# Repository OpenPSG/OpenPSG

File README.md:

# OpenPSG

## Notes

This tool will only work on Google Chrome, Microsoft Edge or Android. It will
not work on Firefox, Safari, or any other browser.

On Linux you'll need to explicitly enable the Web Bluetooth API in your
browser settings. This is still an experimental feature due to historical
issues with the Linux Bluetooth stack. If you are running an up-to-date
Linux install you'll be totally fine to turn it on!

https://github.com/WebBluetoothCG/web-bluetooth/blob/main/implementation-status.md

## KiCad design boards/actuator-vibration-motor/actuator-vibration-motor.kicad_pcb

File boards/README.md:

# Board Files

The boards are designed with/for KiCad v8.0.x

## JLCPCB Manufacturing and Assembly

### Gerbers and Drill Files

Follow the instructions here:

https://jlcpcb.com/help/article/how-to-generate-gerber-and-drill-files-in-kicad-8

### Bill of Materials (BOM)

In eeschema, go to `Tools` -> `Generate Bill of Materials`.

In the edit tab configure the fields as follows:

Then click on `Generate` and save the file as `<board>-bom.csv` in the manufacturing files folder.

### Pick and Place (CPL)

In pcbnew, go to `File` -> `Fabrication Outputs` -> `Component Placement (.pos, .gbr)...`.

Configure the fields as follows:

Then click on `Generate`.

### Convert to JLCPCB Format

Use my [jlcfabtool](https://github.com/dpeckett/jlcfabtool) utility to convert the files to the JLCPCB format.

```sh
jlcfabtool bom convert <board>-bom.csv
jlcfabtool placement convert <board>-all-pos.csv
```

### Create the Archive

```sh
cd <board>
zip -r ../$(basename "$(pwd)").zip ./*
```

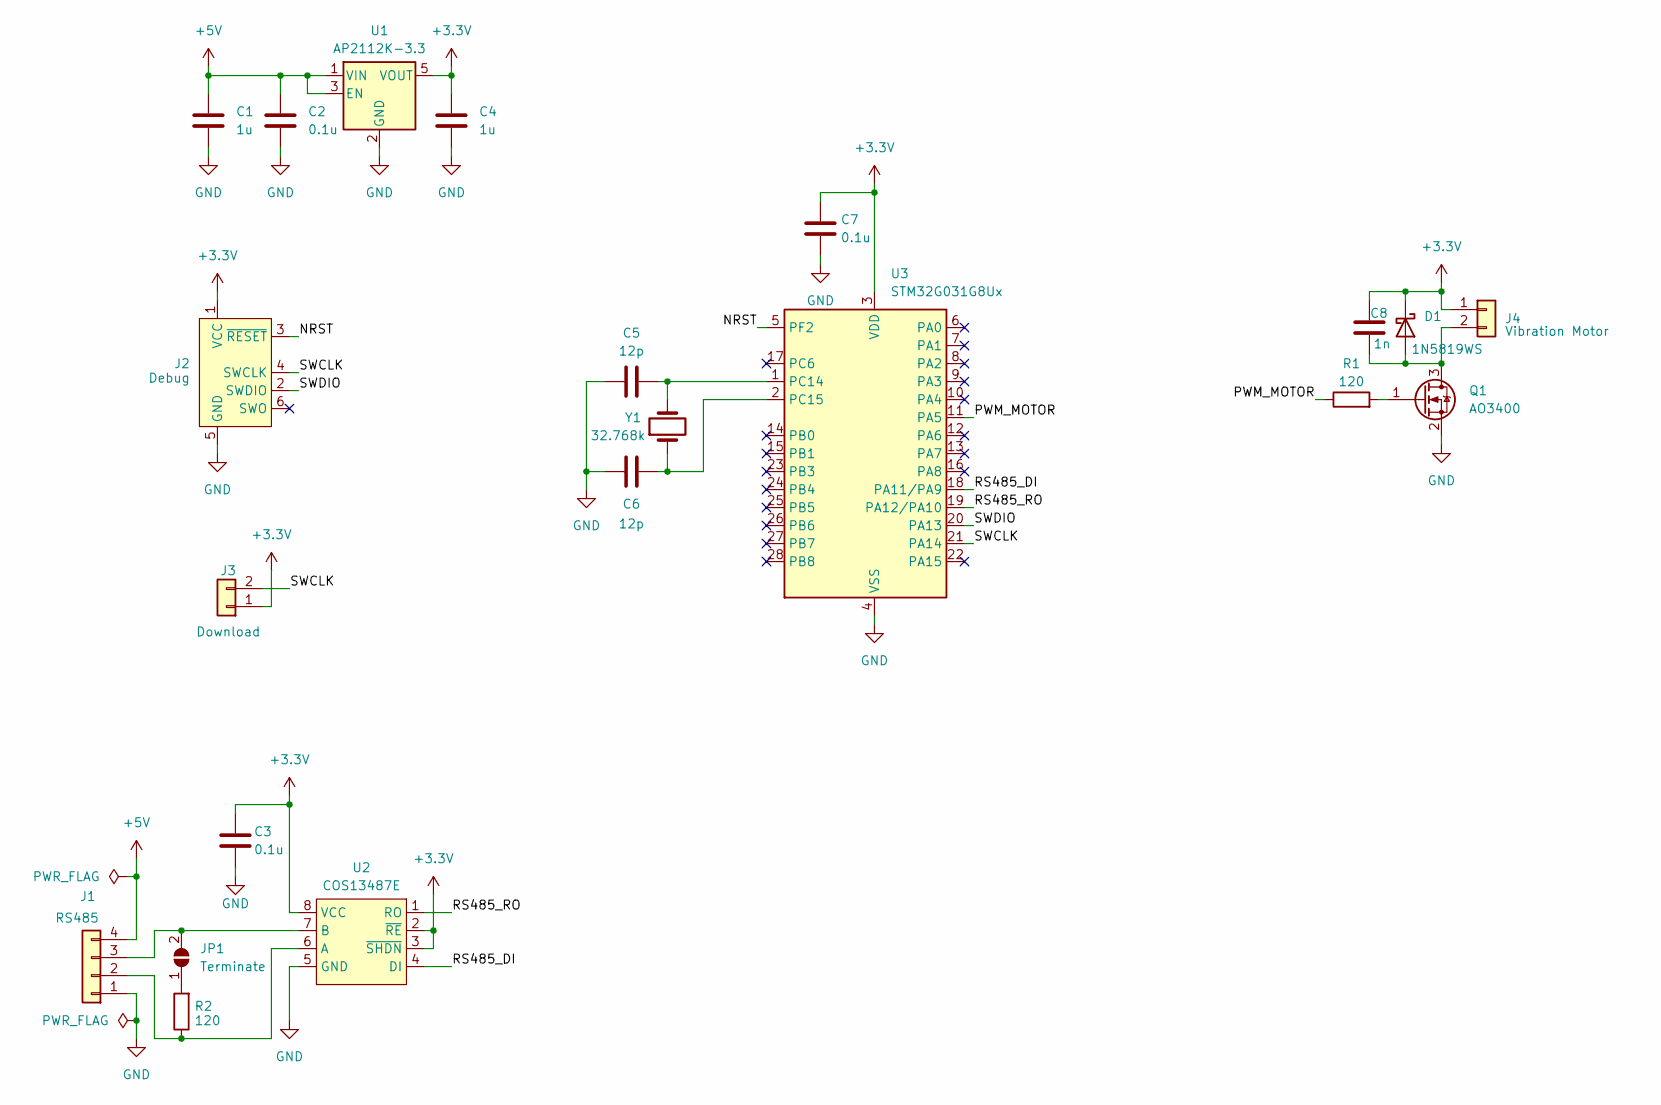
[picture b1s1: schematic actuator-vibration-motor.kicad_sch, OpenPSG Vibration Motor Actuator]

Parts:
C1, C4: 1u; C_0402_1005Metric; LCSC PN C52923
C2, C3, C7: 0.1u; C_0402_1005Metric; LCSC PN C1525
C5, C6: 12p; C_0402_1005Metric; LCSC PN C1547
C8: 1n; C_0402_1005Metric; LCSC PN C1523
D1: 1N5819WS; D_SOD-323; LCSC PN C191023
J1: RS485; JST_PH_S4B-PH-K_1x04_P2.00mm_Horizontal; LCSC PN C2908636
J2: Debug; Tag-Connect_TC2030-IDC-NL_2x03_P1.27mm_Vertical
J3: Download; PinHeader_1x02_P1.27mm_Vertical; LCSC PN C703015
J4: Vibration Motor; JST_PH_S2B-PH-K_1x02_P2.00mm_Horizontal; LCSC PN C2908634
JP1: Terminate; SolderJumper-2_P1.3mm_Open_RoundedPad1.0x1.5mm
Q1: AO3400; SOT-23; LCSC PN C20917
R1, R2: 120; R_0402_1005Metric; LCSC PN C25079
U1: AP2112K-3.3; SOT-23-5; LCSC PN C51118
U2: COS13487E; SOP-8_3.9x4.9mm_P1.27mm; LCSC PN C22466040
U3: STM32G031G8Ux; QFN-28_4x4mm_P0.5mm; LCSC PN C432211
Y1: 32.768k; Crystal_SMD_3215-2Pin_3.2x1.5mm; LCSC PN C32346

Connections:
+3.3V: C3.1, C4.1, C7.1, C8.1, D1.1 (K), J2.1 (VCC), J3.1, J4.1, U1.5 (VOUT), U2.2 (~RE), U2.3 (~SHDN), U2.8 (VCC), U3.3 (VDD)
+5V: C1.1, C2.1, J1.4, U1.1 (VIN), U1.3 (EN)
/NRST: J2.3 (~RESET), U3.5 (PF2)
/PWM_MOTOR: R1.1, U3.11 (PA5)
/RS485_DI: U2.4 (DI), U3.18 (PA11/PA9)
/RS485_RO: U2.1 (RO), U3.19 (PA12/PA10)
/SWCLK: J2.4 (SWCLK), J3.2, U3.21 (PA14)
/SWDIO: J2.2 (SWDIO), U3.20 (PA13)
GND: C1.2, C2.2, C3.2, C4.2, C5.2, C6.1, C7.2, J1.1, J2.5 (GND), Q1.2 (S), U1.2 (GND), U2.5 (GND), U3.4 (VSS)
unnamed: C8.2, D1.2 (A), J4.2, Q1.3 (D)
unnamed: J1.2, R2.1, U2.6 (A)
unnamed: J1.3, JP1.2 (B), U2.7 (B)
unnamed: JP1.1 (A), R2.2
unnamed: Q1.1 (G), R1.2
unnamed: C5.1, U3.1 (PC14), Y1.2
unnamed: C6.2, U3.2 (PC15), Y1.1

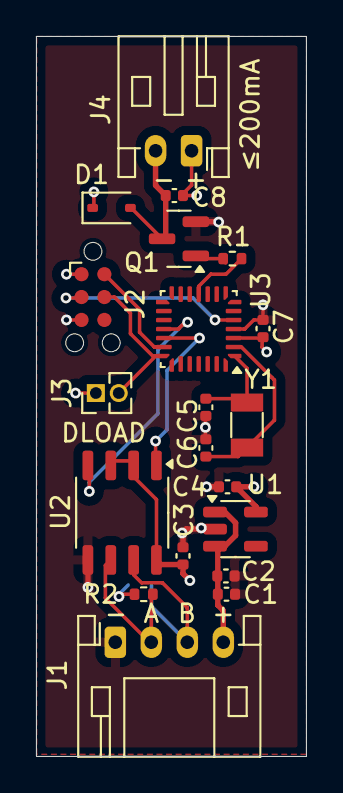
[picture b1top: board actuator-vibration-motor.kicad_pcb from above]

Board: 4 copper layers, 15.0 x 40.0 mm, 21 parts (1 on the bottom side), 16 nets.

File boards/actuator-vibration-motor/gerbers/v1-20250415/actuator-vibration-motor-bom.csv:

"Reference","Value","Datasheet","Footprint","Qty","DNP","LCSC PN"
"C1,C4","1u","~","Capacitor_SMD:C_0402_1005Metric","2","","C52923"
"C2,C3,C7","0.1u","~","Capacitor_SMD:C_0402_1005Metric","3","","C1525"
"C5,C6","12p","~","Capacitor_SMD:C_0402_1005Metric","2","","C1547"
"C8","1n","~","Capacitor_SMD:C_0402_1005Metric","1","","C1523"
"D1","1N5819WS","https://datasheet.lcsc.com/lcsc/2204281430_Guangdong-Hottech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","Diode_SMD:D_SOD-323","1","","C191023"
"J1","RS485","~","Connector_JST:JST_PH_S4B-PH-K_1x04_P2.00mm_Horizontal","1","","C2908636"
"J3","Download","~","Connector_PinHeader_1.27mm:PinHeader_1x02_P1.27mm_Vertical","1","","C703015"
"J4","Vibration Motor","~","Connector_JST:JST_PH_S2B-PH-K_1x02_P2.00mm_Horizontal","1","","C2908634"
"JP1","Terminate","~","Jumper:SolderJumper-2_P1.3mm_Open_RoundedPad1.0x1.5mm","1","",""
"Q1","AO3400","http://www.aosmd.com/pdfs/datasheet/AO3400A.pdf","Package_TO_SOT_SMD:SOT-23","1","","C20917"
"R1,R2","120","~","Resistor_SMD:R_0402_1005Metric","2","","C25079"
"U1","AP2112K-3.3","https://www.diodes.com/assets/Datasheets/AP2112.pdf","Package_TO_SOT_SMD:SOT-23-5","1","","C51118"
"U2","COS13487E","","Package_SO:SOP-8_3.9x4.9mm_P1.27mm","1","","C22466040"
"U3","STM32G031G8Ux","https://www.st.com/resource/en/datasheet/stm32g031g8.pdf","Package_DFN_QFN:QFN-28_4x4mm_P0.5mm","1","","C432211"
"Y1","32.768k","~","Crystal:Crystal_SMD_3215-2Pin_3.2x1.5mm","1","","C32346"

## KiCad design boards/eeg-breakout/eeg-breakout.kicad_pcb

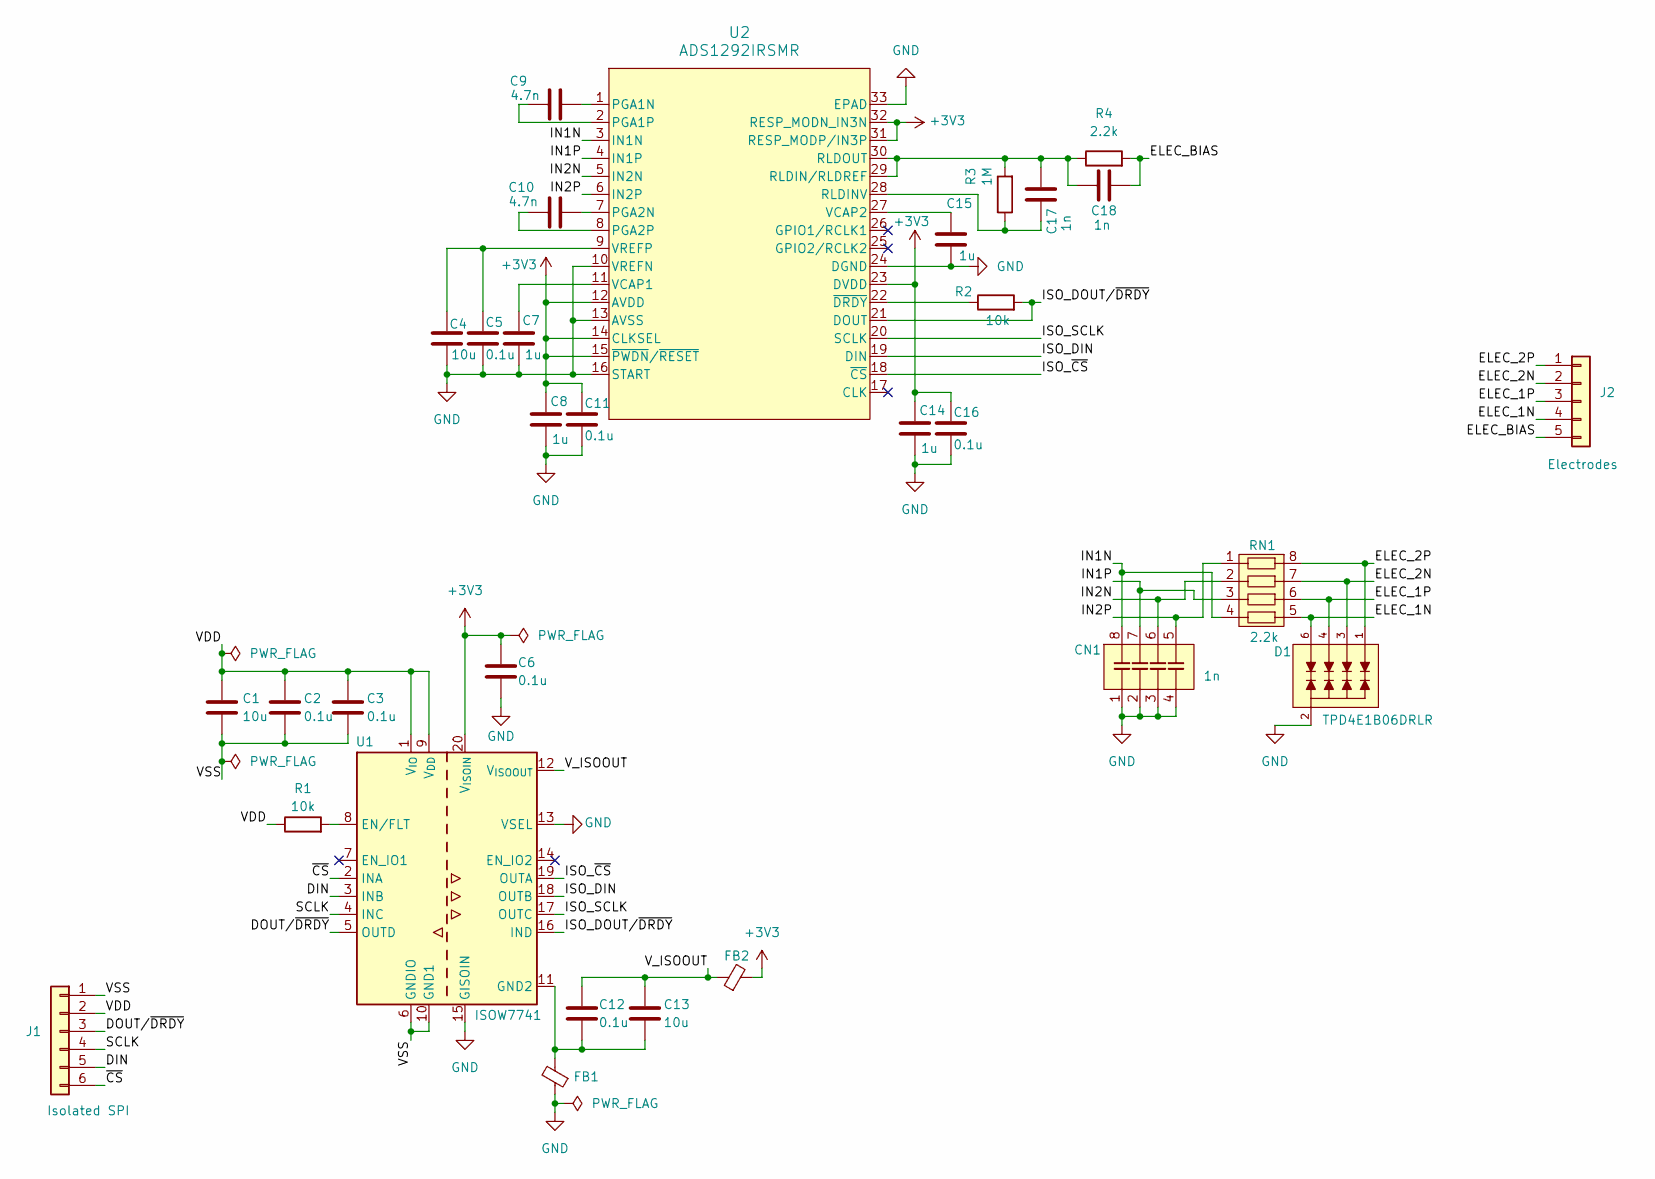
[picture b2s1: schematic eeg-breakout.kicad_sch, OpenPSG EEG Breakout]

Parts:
C1, C4, C13: 10u; C_0603_1608Metric; LCSC PN C19702
C2, C3, C5, C6, C11, C12, C16: 0.1u; C_0402_1005Metric; LCSC PN C1525
C7, C8, C14, C15: 1u; C_0402_1005Metric; LCSC PN C52923
C9, C10: 4.7n; C_0402_1005Metric; LCSC PN C1538
C17, C18: 1n; C_0402_1005Metric; LCSC PN C1523
CN1: 1n; R_Array_Convex_4x0612; LCSC PN C2649771
D1: TPD4E1B06DRLR; SOT-563; LCSC PN C1972953
FB1, FB2: FerriteBead_Small; L_0603_1608Metric; LCSC PN C19330
J1: Isolated SPI; PinHeader_1x06_P2.54mm_Horizontal
J2: Electrodes; PinHeader_1x05_P2.54mm_Horizontal
R1, R2: 10k; R_0402_1005Metric; LCSC PN C25744
R3: 1M; R_0402_1005Metric; LCSC PN C26083
R4: 2.2k; R_0402_1005Metric; LCSC PN C25879
RN1: 2.2k; R_Array_Convex_4x0402; LCSC PN C326864
U1: ISOW7741; SOIC-20W_7.5x12.8mm_P1.27mm; LCSC PN C5216399
U2: ADS1292IRSMR; VQFN-32-1EP_4x4mm_P0.4mm_EP2.8x2.8mm; LCSC PN C544416

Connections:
+3V3: C6.1, C8.1, C11.1, C14.1, C16.1, FB2.2, U1.20 (V_{ISOIN}), U2.12 (AVDD), U2.14 (CLKSEL), U2.15 (~PWDN/~RESET), U2.23 (DVDD), U2.31 (RESP_MODP/IN3P), U2.32 (RESP_MODN_IN3N)
/DIN: J1.5, U1.3 (INB)
/DOUT/~DRDY: J1.3, U1.5 (OUTD)
/ELEC_1N: D1.6, J2.4, RN1.5
/ELEC_1P: D1.4, J2.3, RN1.6
/ELEC_2N: D1.3, J2.2, RN1.7
/ELEC_2P: D1.1, J2.1, RN1.8
/ELEC_BIAS: C18.2, J2.5, R4.2
/IN1N: CN1.8, RN1.4, U2.3 (IN1N)
/IN1P: CN1.7, RN1.3, U2.4 (IN1P)
/IN2N: CN1.6, RN1.2, U2.5 (IN2N)
/IN2P: CN1.5, RN1.1, U2.6 (IN2P)
/ISO_DIN: U1.18 (OUTB), U2.19 (DIN)
/ISO_DOUT/~DRDY: R2.2, U1.16 (IND), U2.21 (DOUT)
/ISO_SCLK: U1.17 (OUTC), U2.20 (SCLK)
/ISO_~CS: U1.19 (OUTA), U2.18 (~CS)
/SCLK: J1.4, U1.4 (INC)
/VDD: C1.1, C2.1, C3.1, J1.2, R1.1, U1.1 (V_{IO}), U1.9 (V_{DD})
/VSS: C1.2, C2.2, C3.2, J1.1, U1.6 (GNDIO), U1.10 (GND1)
/V_ISOOUT: C12.1, C13.1, FB2.1, U1.12 (V_{ISOOUT})
/~CS: J1.6, U1.2 (INA)
GND: C4.2, C5.2, C6.2, C7.1, C8.2, C11.2, C14.2, C15.2, C16.2, CN1.1, CN1.2, CN1.3, CN1.4, D1.2, FB1.1, U1.13 (VSEL), U1.15 (GISOIN), U2.10 (VREFN), U2.13 (AVSS), U2.16 (START), U2.24 (DGND), U2.33 (EPAD)
unnamed: R1.2, U1.8 (EN/FLT)
unnamed: C12.2, C13.2, FB1.2, U1.11 (GND2)
unnamed: C9.2, U2.1 (PGA1N)
unnamed: C9.1, U2.2 (PGA1P)
unnamed: C10.2, U2.7 (PGA2N)
unnamed: C10.1, U2.8 (PGA2P)
unnamed: C17.1, R3.1, U2.28 (RLDINV)
unnamed: C17.2, C18.1, R3.2, R4.1, U2.29 (RLDIN/RLDREF), U2.30 (RLDOUT)
unnamed: C7.2, U2.11 (VCAP1)
unnamed: C15.1, U2.27 (VCAP2)
unnamed: C4.1, C5.1, U2.9 (VREFP)
unnamed: R2.1, U2.22 (~DRDY)

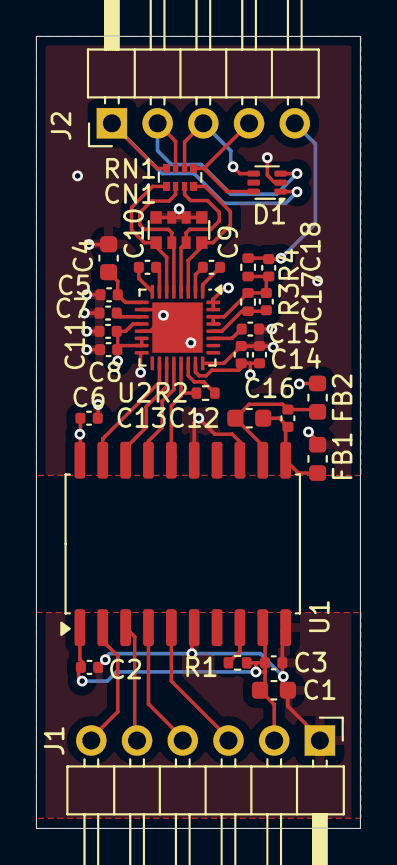
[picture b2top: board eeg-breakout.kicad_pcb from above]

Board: 4 copper layers, 18.0 x 44.0 mm, 31 parts (0 on the bottom side), 34 nets.

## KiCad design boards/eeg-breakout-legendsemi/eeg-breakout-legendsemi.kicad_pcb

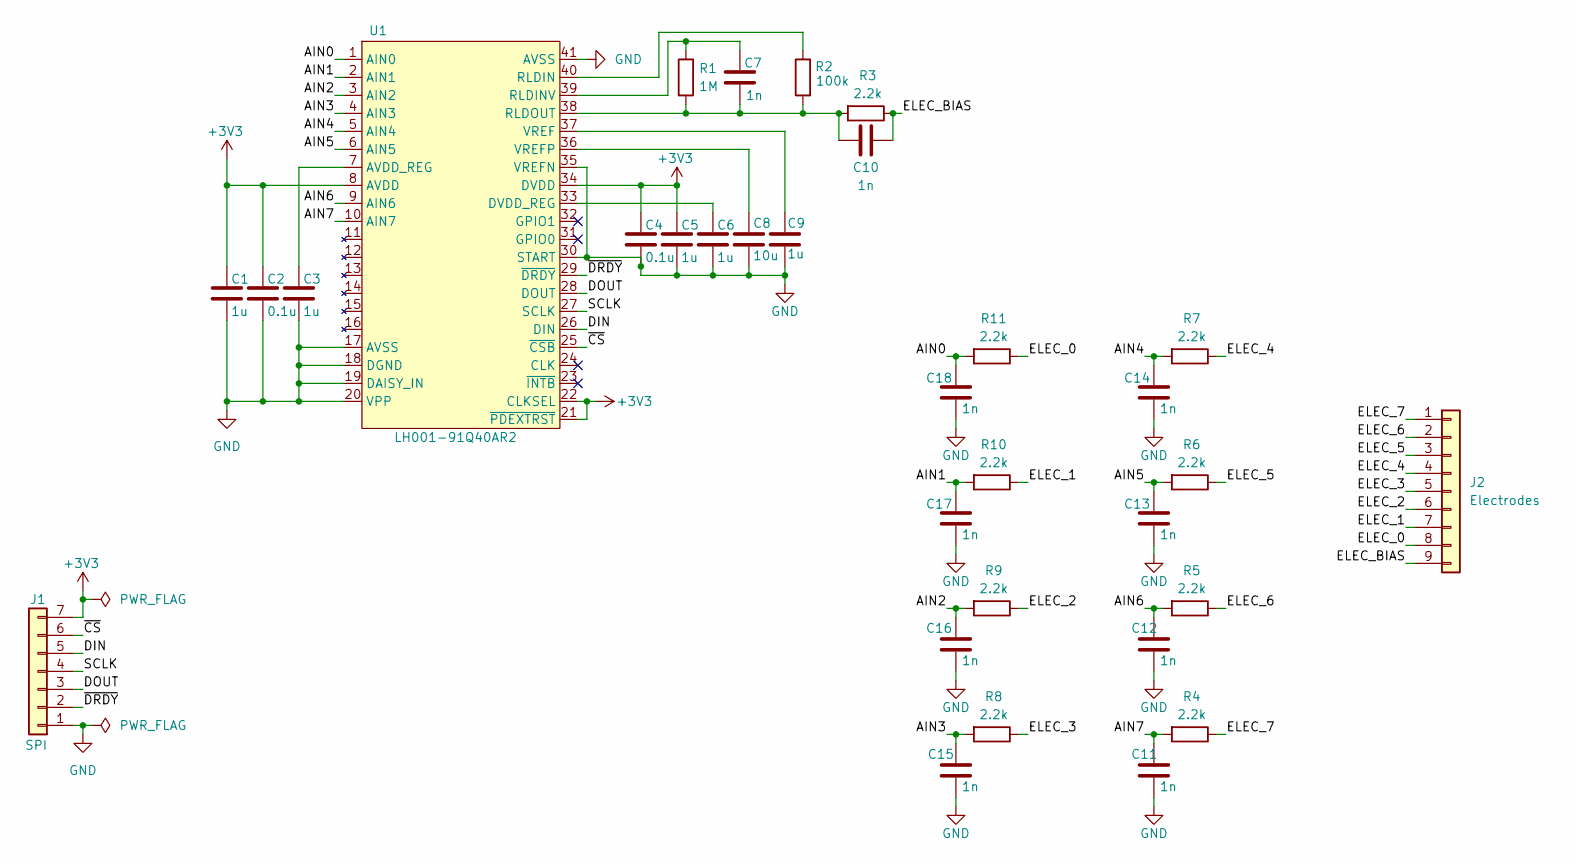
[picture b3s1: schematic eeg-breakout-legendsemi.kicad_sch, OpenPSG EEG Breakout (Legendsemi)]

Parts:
C1, C3, C5, C6, C9: 1u; C_0402_1005Metric; LCSC PN C52923
C2, C4: 0.1u; C_0402_1005Metric; LCSC PN C1525
C7, C10, C11, C12, C13, C14, C15, C16, C17, C18: 1n; C_0402_1005Metric; LCSC PN C1523
C8: 10u; C_0603_1608Metric; LCSC PN C19702
J1: SPI; PinHeader_1x07_P2.54mm_Horizontal
J2: Electrodes; PinHeader_1x09_P2.54mm_Horizontal
R1: 1M; R_0402_1005Metric; LCSC PN C26083
R2: 100k; R_0402_1005Metric; LCSC PN C25741
R3, R4, R5, R6, R7, R8, R9, R10, R11: 2.2k; R_0402_1005Metric; LCSC PN C25879
U1: LH001-91Q40AR2; QFN-40-1EP_5x5mm_P0.4mm_EP3.6x3.6mm; LCSC PN C42459077

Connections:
+3V3: C1.1, C2.1, C4.1, C5.1, J1.7, U1.8 (AVDD), U1.21 (~PDEXTRST), U1.22 (CLKSEL), U1.34 (DVDD)
/AIN0: C18.1, R11.2, U1.1 (AIN0)
/AIN1: C17.1, R10.2, U1.2 (AIN1)
/AIN2: C16.1, R9.2, U1.3 (AIN2)
/AIN3: C15.1, R8.2, U1.4 (AIN3)
/AIN4: C14.1, R7.2, U1.5 (AIN4)
/AIN5: C13.1, R6.2, U1.6 (AIN5)
/AIN6: C12.1, R5.2, U1.9 (AIN6)
/AIN7: C11.1, R4.2, U1.10 (AIN7)
/DIN: J1.5, U1.26 (DIN)
/DOUT: J1.3, U1.28 (DOUT)
/ELEC_0: J2.8, R11.1
/ELEC_1: J2.7, R10.1
/ELEC_2: J2.6, R9.1
/ELEC_3: J2.5, R8.1
/ELEC_4: J2.4, R7.1
/ELEC_5: J2.3, R6.1
/ELEC_6: J2.2, R5.1
/ELEC_7: J2.1, R4.1
/ELEC_BIAS: C10.1, J2.9, R3.1
/SCLK: J1.4, U1.27 (SCLK)
/~CS: J1.6, U1.25 (~CSB)
/~DRDY: J1.2, U1.29 (~DRDY)
GND: C1.2, C2.2, C3.2, C4.2, C5.2, C6.2, C8.2, C9.2, C11.2, C12.2, C13.2, C14.2, C15.2, C16.2, C17.2, C18.2, J1.1, U1.17 (AVSS), U1.18 (DGND), U1.19 (DAISY_IN), U1.20 (VPP), U1.30 (START), U1.35 (VREFN), U1.41 (AVSS)
unnamed: C3.1, U1.7 (AVDD_REG)
unnamed: C6.1, U1.33 (DVDD_REG)
unnamed: R2.1, U1.40 (RLDIN)
unnamed: C7.1, R1.1, U1.39 (RLDINV)
unnamed: C7.2, C10.2, R1.2, R2.2, R3.2, U1.38 (RLDOUT)
unnamed: C9.1, U1.37 (VREF)
unnamed: C8.1, U1.36 (VREFP)

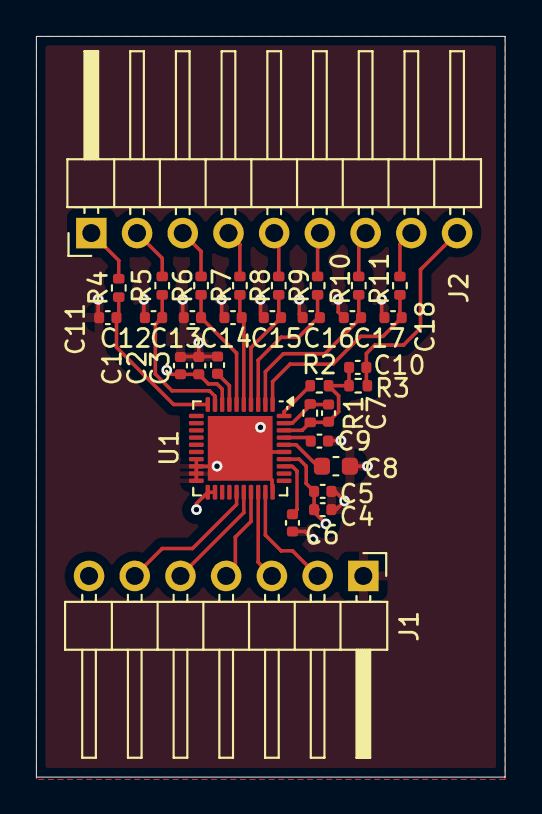
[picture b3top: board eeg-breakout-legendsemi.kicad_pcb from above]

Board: 4 copper layers, 26.0 x 41.1 mm, 32 parts (0 on the bottom side), 31 nets.

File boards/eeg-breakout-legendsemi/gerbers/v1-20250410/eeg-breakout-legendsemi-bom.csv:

"Reference","Value","Datasheet","Footprint","Qty","DNP","LCSC PN"
"C1,C3,C5,C6,C9","1u","~","Capacitor_SMD:C_0402_1005Metric","5","","C52923"
"C2,C4","0.1u","~","Capacitor_SMD:C_0402_1005Metric","2","","C1525"
"C7,C10,C11,C12,C13,C14,C15,C16,C17,C18","1n","~","Capacitor_SMD:C_0402_1005Metric","10","","C1523"
"C8","10u","~","Capacitor_SMD:C_0603_1608Metric","1","","C19702"
"R1","1M","~","Resistor_SMD:R_0402_1005Metric","1","","C26083"
"R2","100k","~","Resistor_SMD:R_0402_1005Metric","1","","C25741"
"R3,R4,R5,R6,R7,R8,R9,R10,R11","2.2k","~","Resistor_SMD:R_0402_1005Metric","9","","C25879"
"U1","LH001-91Q40AR2","","Package_DFN_QFN:QFN-40-1EP_5x5mm_P0.4mm_EP3.6x3.6mm","1","","C42459077"

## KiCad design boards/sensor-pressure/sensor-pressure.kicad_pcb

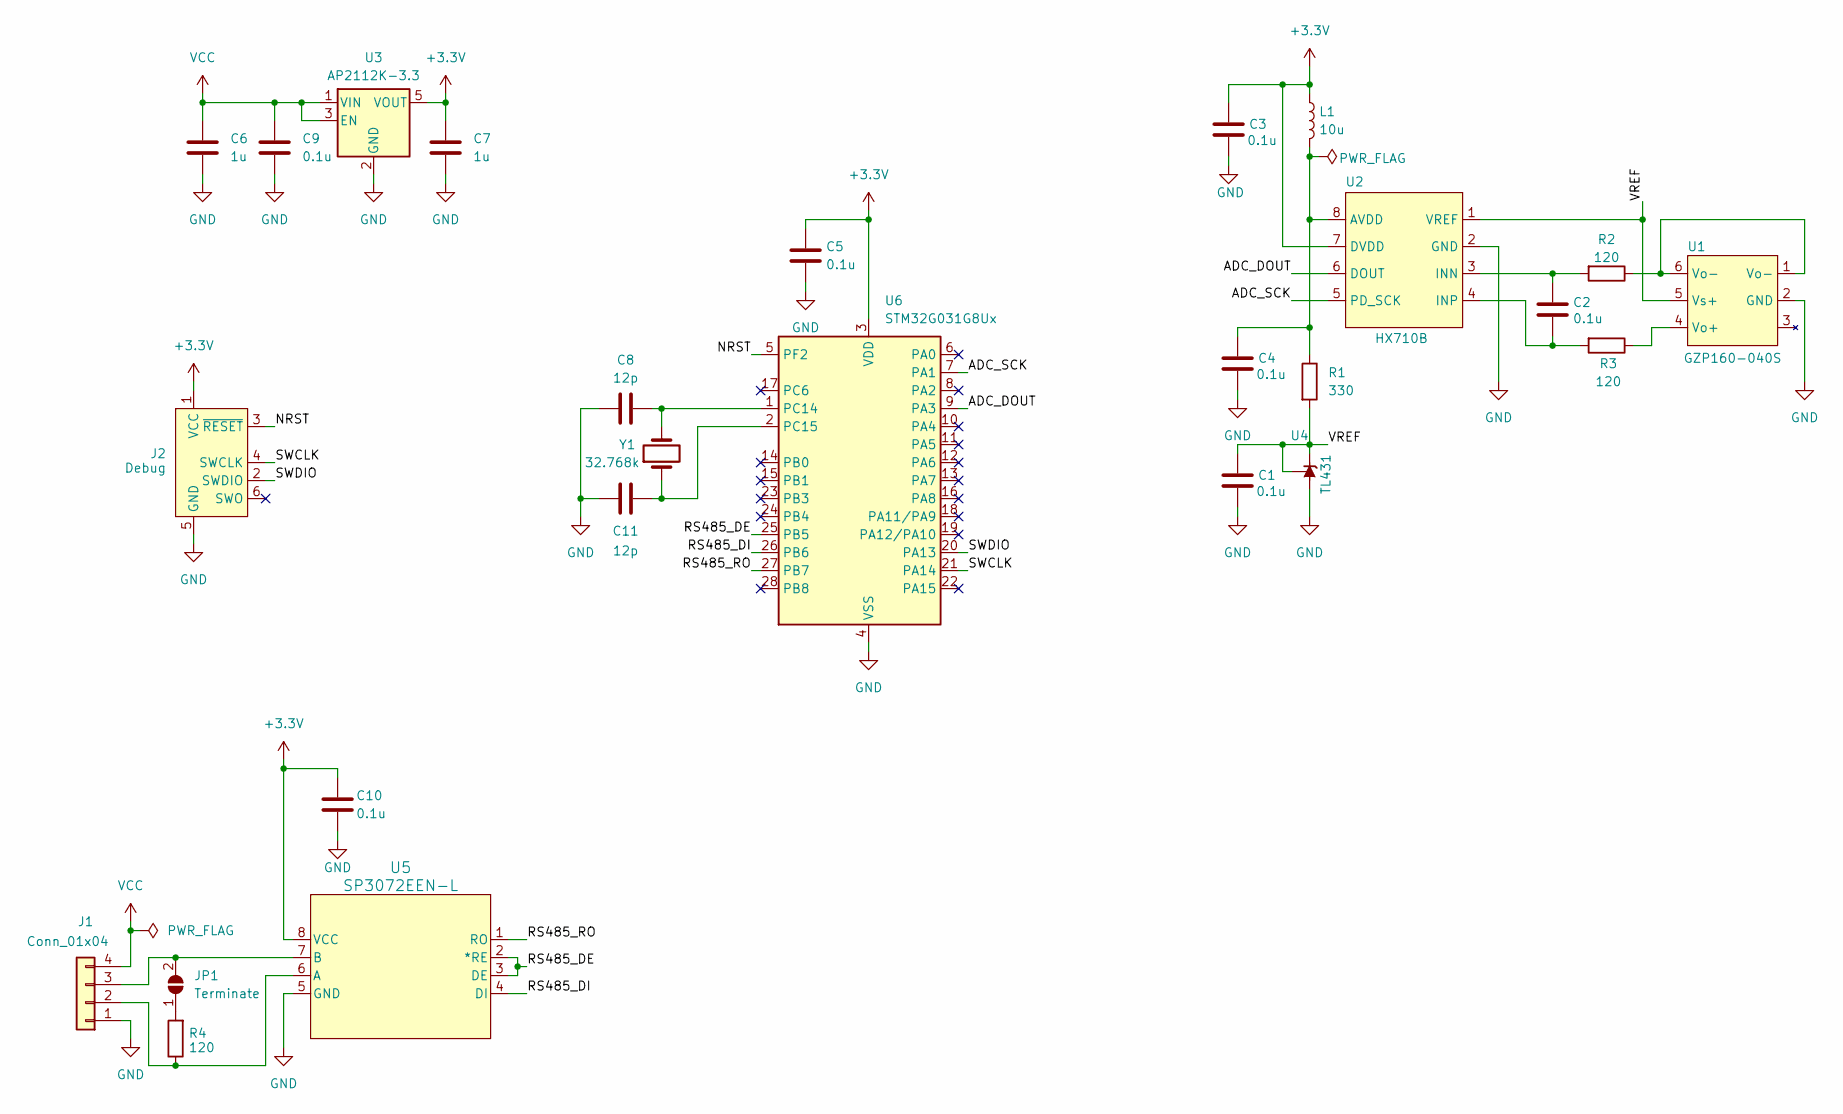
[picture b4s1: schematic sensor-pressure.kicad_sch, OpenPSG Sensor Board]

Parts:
C1, C2, C3, C4, C5, C9, C10: 0.1u; C_0402_1005Metric; LCSC PN C1525
C6, C7: 1u; C_0402_1005Metric; LCSC PN C52923
C8, C11: 12p; C_0402_1005Metric; LCSC PN C1547
J1: Conn_01x04; JST_PH_S4B-PH-K_1x04_P2.00mm_Horizontal; LCSC PN C2908636
J2: Debug; Tag-Connect_TC2030-IDC-NL_2x03_P1.27mm_Vertical
JP1: Terminate; SolderJumper-2_P1.3mm_Open_RoundedPad1.0x1.5mm
L1: 10u; L_0805_2012Metric; LCSC PN C1046
R1: 330; R_0402_1005Metric; LCSC PN C25104
R2, R3, R4: 120; R_0402_1005Metric; LCSC PN C25079
U1: GZP160-040S; LCSC PN C3037979
U2: HX710B; SOP-8_3.9x4.9mm_P1.27mm; LCSC PN C68417
U3: AP2112K-3.3; SOT-23-5; LCSC PN C51118
U4: TL431; SOT-23; LCSC PN C23892
U5: SP3072EEN-L; SOP-8_3.9x4.9mm_P1.27mm; LCSC PN C2692300
U6: STM32G031G8Ux; QFN-28_4x4mm_P0.5mm; LCSC PN C432211
Y1: 32.768k; Crystal_SMD_3215-2Pin_3.2x1.5mm; LCSC PN C32346

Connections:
+3.3V: C3.1, C5.1, C7.1, C10.1, J2.1 (VCC), L1.1, U2.7 (DVDD), U3.5 (VOUT), U5.8 (VCC), U6.3 (VDD)
/ADC_DOUT: U2.6 (DOUT), U6.9 (PA3)
/ADC_SCK: U2.5 (PD_SCK), U6.7 (PA1)
/NRST: J2.3 (~RESET), U6.5 (PF2)
/RS485_DE: U5.2 (*RE), U5.3 (DE), U6.25 (PB5)
/RS485_DI: U5.4 (DI), U6.26 (PB6)
/RS485_RO: U5.1 (RO), U6.27 (PB7)
/SWCLK: J2.4 (SWCLK), U6.21 (PA14)
/SWDIO: J2.2 (SWDIO), U6.20 (PA13)
/VREF: C1.1, R1.2, U1.5 (Vs+), U2.1 (VREF), U4.1 (K), U4.2 (REF)
GND: C1.2, C3.2, C4.2, C5.2, C6.2, C7.2, C8.2, C9.2, C10.2, C11.1, J1.1, J2.5 (GND), U1.2 (GND), U2.2 (GND), U3.2 (GND), U4.3 (A), U5.5 (GND), U6.4 (VSS)
unnamed: J1.2, R4.1, U5.6 (A)
unnamed: J1.3, JP1.2 (B), U5.7 (B)
unnamed: JP1.1 (A), R4.2
unnamed: R2.1, U1.1 (Vo-), U1.6 (Vo-)
unnamed: R3.1, U1.4 (Vo+)
unnamed: C4.1, L1.2, R1.1, U2.8 (AVDD)
unnamed: C2.1, R2.2, U2.3 (INN)
unnamed: C2.2, R3.2, U2.4 (INP)
unnamed: C8.1, U6.1 (PC14), Y1.2
unnamed: C11.2, U6.2 (PC15), Y1.1
VCC: C6.1, C9.1, J1.4, U3.1 (VIN), U3.3 (EN)

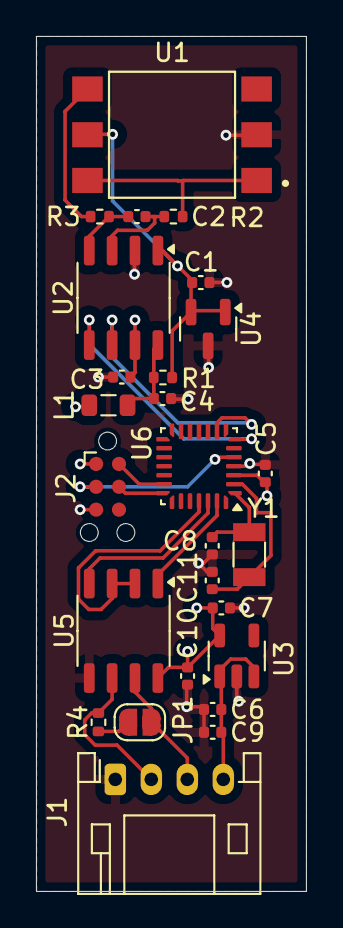
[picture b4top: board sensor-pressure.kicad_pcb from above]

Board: 4 copper layers, 15.0 x 47.5 mm, 26 parts (0 on the bottom side), 22 nets.

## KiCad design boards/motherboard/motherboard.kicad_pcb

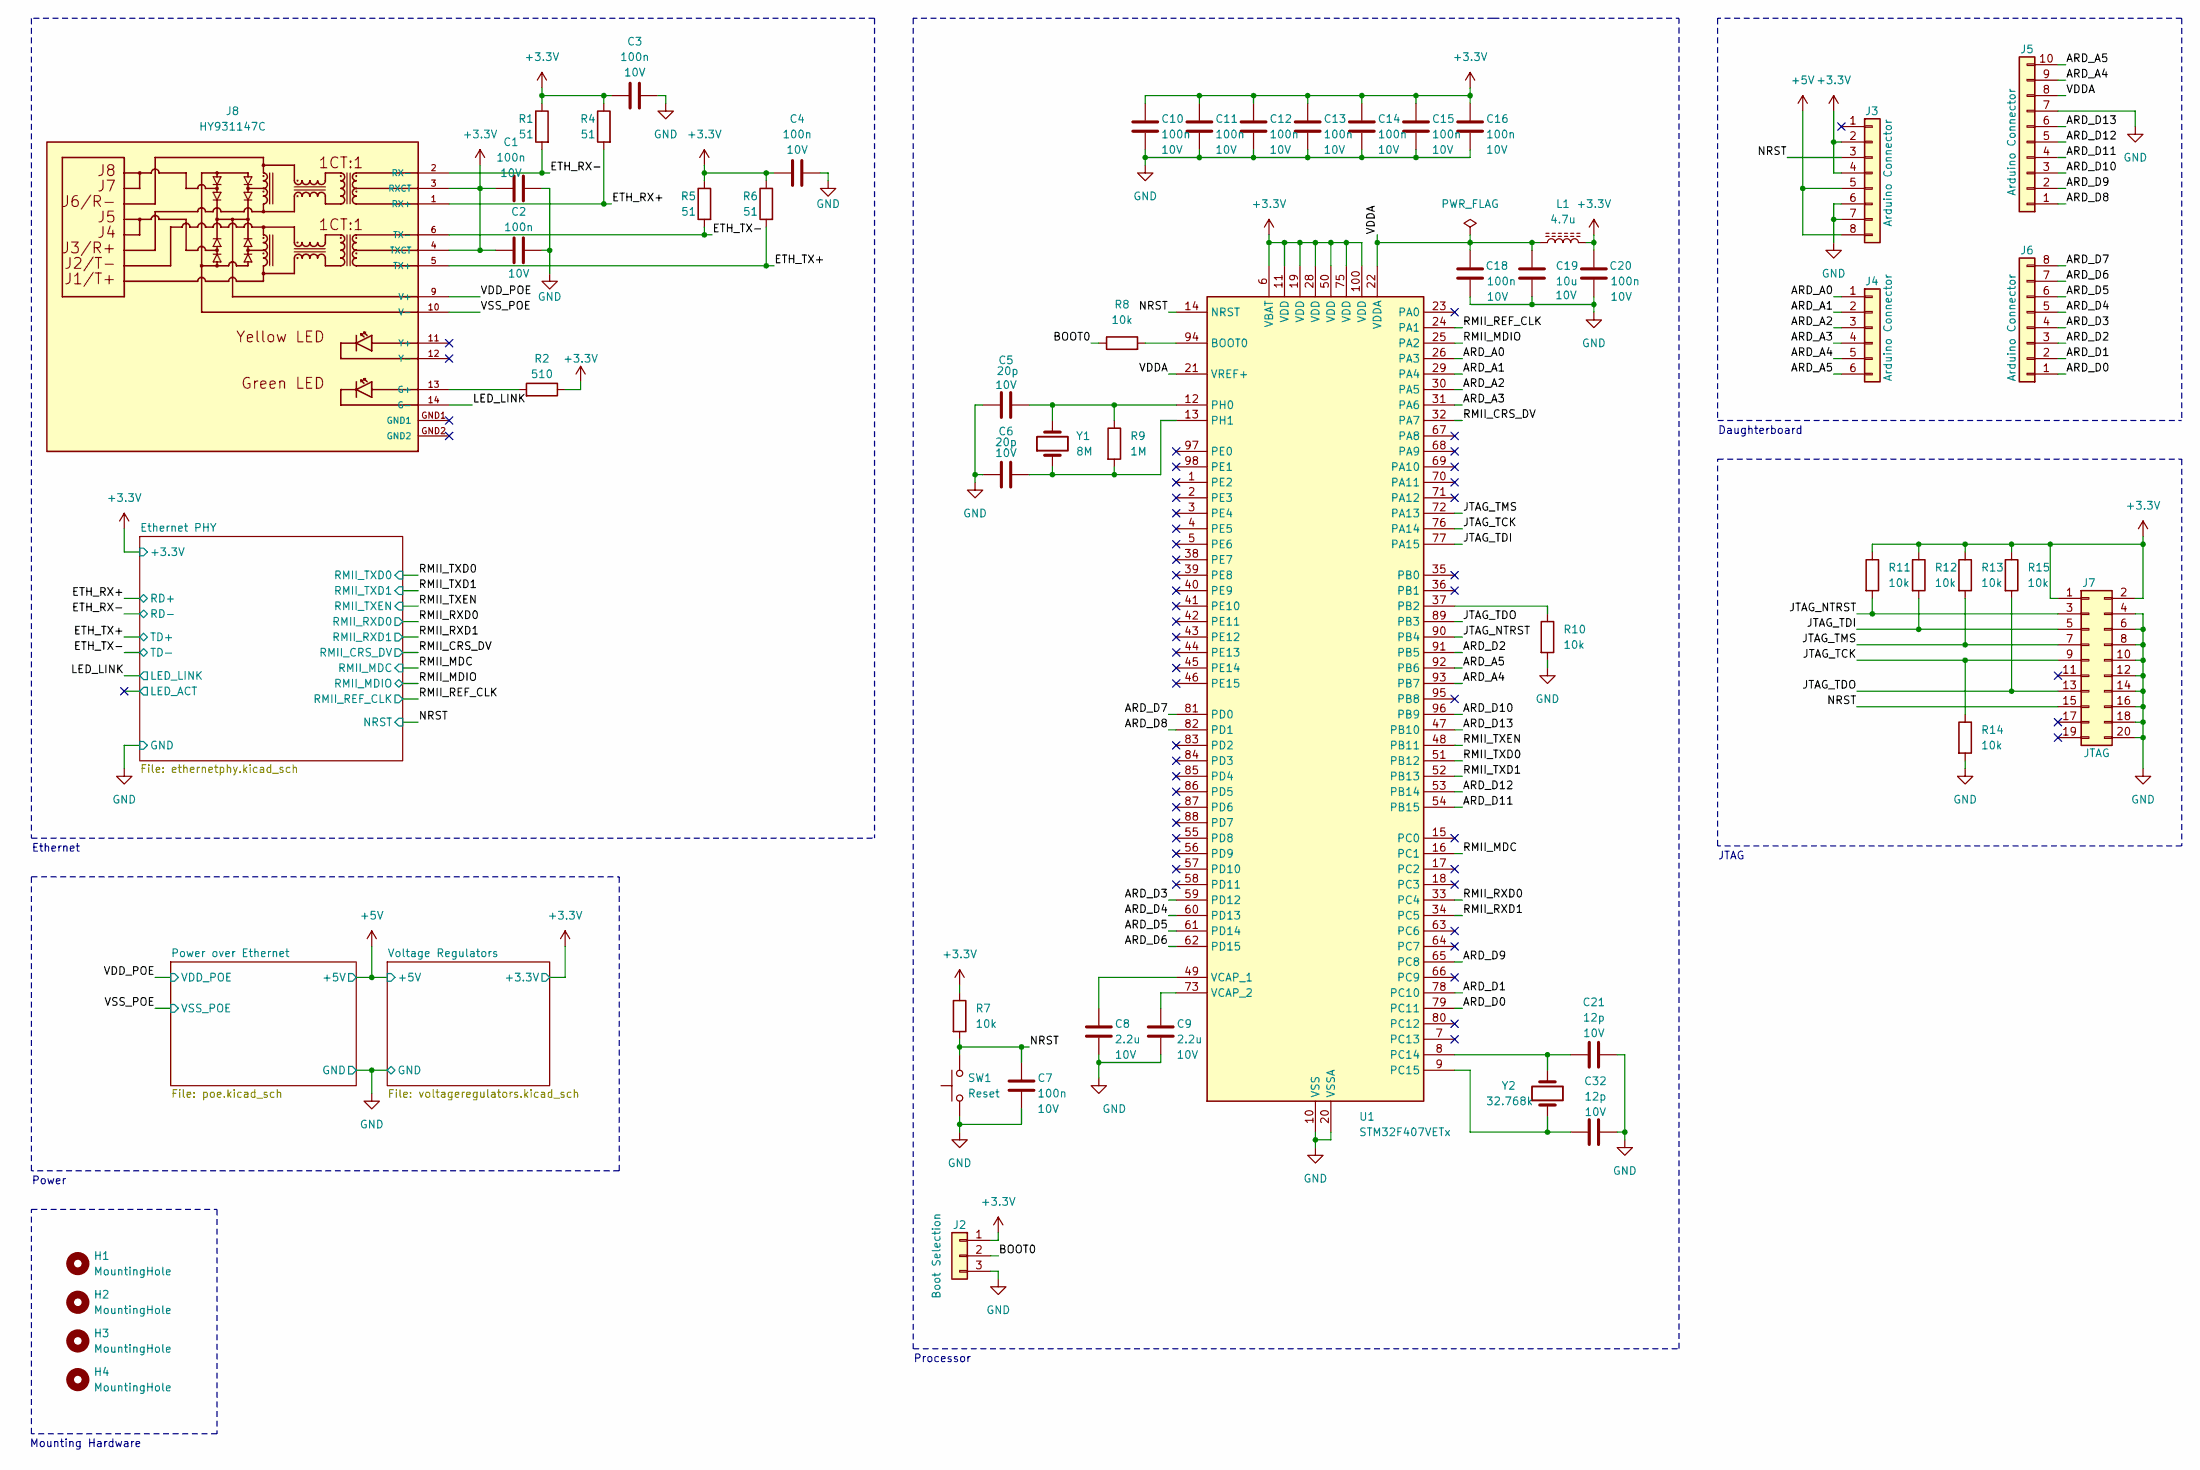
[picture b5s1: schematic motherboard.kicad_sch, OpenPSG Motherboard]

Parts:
C1, C2, C3, C4, C7, C10, C11, C12, C13, C14, C15, C16, C18, C20: 100n; C_0603_1608Metric; Voltage Rating 10V; LCSC PN C14663
C5, C6: 20p; C_0603_1608Metric; Voltage Rating 10V; LCSC PN C1648
C8, C9: 2.2u; C_0603_1608Metric; Voltage Rating 10V; LCSC PN C23630
C19: 10u; C_0603_1608Metric; Voltage Rating 10V; LCSC PN C96446
C21, C32: 12p; C_0603_1608Metric; Voltage Rating 10V; LCSC PN C38523
H1, H2, H3, H4: MountingHole; MountingHole_3.2mm_M3
J2: Boot Selection; PinHeader_1x03_P2.54mm_Vertical; LCSC PN C2937625
J3, J6: Arduino Connector; PinSocket_1x08_P2.54mm_Vertical; LCSC PN C2897371
J4: Arduino Connector; PinSocket_1x06_P2.54mm_Vertical; LCSC PN C2897369
J5: Arduino Connector; PinSocket_1x10_P2.54mm_Vertical; LCSC PN C2897373
J7: JTAG; IDC-Header_2x10_P2.54mm_Vertical; LCSC PN C5372868
J8: HY931147C; LCSC PN C91754
L1: 4.7u; L_0805_2012Metric; LCSC PN C86088
R1, R4, R5, R6: 51; R_0603_1608Metric; LCSC PN C23197
R2: 510; R_0603_1608Metric; LCSC PN C23193
R7, R8, R10, R11, R12, R13, R14, R15: 10k; R_0603_1608Metric; LCSC PN C25804
R9: 1M; R_0603_1608Metric; LCSC PN C22935
SW1: Reset; SW_SPST_SKQG_WithStem; LCSC PN C318884
U1: STM32F407VETx; LQFP-100_14x14mm_P0.5mm; LCSC PN C28730
Y1: 8M; Crystal_SMD_5032-2Pin_5.0x3.2mm; LCSC PN C115962
Y2: 32.768k; Crystal_SMD_3215-2Pin_3.2x1.5mm; LCSC PN C32346

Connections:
+3.3V: C1.2, C2.2, C3.1, C4.1, C10.1, C11.1, C12.1, C13.1, C14.1, C15.1, C16.1, C20.1, J2.1, J3.2, J3.4, J7.1, J7.2, J8.3 (RXCT), J8.4 (TXCT), L1.1, R1.1, R2.1, R4.1, R5.1, R6.1, R7.1, R11.1, R12.1, R13.1, R15.1, U1.6 (VBAT), U1.11 (VDD), U1.19 (VDD), U1.28 (VDD), U1.50 (VDD), U1.75 (VDD), U1.100 (VDD); also elsewhere on the board
+5V: J3.5, J3.8; also elsewhere on the board
/ARD_A0: J4.1, U1.26 (PA3)
/ARD_A1: J4.2, U1.29 (PA4)
/ARD_A2: J4.3, U1.30 (PA5)
/ARD_A3: J4.4, U1.31 (PA6)
/ARD_A4: J4.5, J5.9, U1.93 (PB7)
/ARD_A5: J4.6, J5.10, U1.92 (PB6)
/ARD_D0: J6.1, U1.79 (PC11)
/ARD_D1: J6.2, U1.78 (PC10)
/ARD_D2: J6.3, U1.91 (PB5)
/ARD_D3: J6.4, U1.59 (PD12)
/ARD_D4: J6.5, U1.60 (PD13)
/ARD_D5: J6.6, U1.61 (PD14)
/ARD_D6: J6.7, U1.62 (PD15)
/ARD_D7: J6.8, U1.81 (PD0)
/ARD_D8: J5.1, U1.82 (PD1)
/ARD_D9: J5.2, U1.65 (PC8)
/ARD_D10: J5.3, U1.96 (PB9)
/ARD_D11: J5.4, U1.54 (PB15)
/ARD_D12: J5.5, U1.53 (PB14)
/ARD_D13: J5.6, U1.47 (PB10)
/BOOT0: J2.2, R8.1
/ETH_RX+: J8.1 (RX+), R4.2; also elsewhere on the board
/ETH_RX-: J8.2 (RX-), R1.2; also elsewhere on the board
/ETH_TX+: J8.5 (TX+), R6.2; also elsewhere on the board
/ETH_TX-: J8.6 (TX-), R5.2; also elsewhere on the board
/JTAG_NTRST: J7.3, R11.2, U1.90 (PB4)
/JTAG_TCK: J7.9, R14.1, U1.76 (PA14)
/JTAG_TDI: J7.5, R12.2, U1.77 (PA15)
/JTAG_TDO: J7.13, R15.2, U1.89 (PB3)
/JTAG_TMS: J7.7, R13.2, U1.72 (PA13)
/LED_LINK: J8.14 (G-); also elsewhere on the board
/NRST: C7.1, J3.3, J7.15, R7.2, SW1.1, U1.14 (NRST); also elsewhere on the board
/RMII_CRS_DV: U1.32 (PA7); also elsewhere on the board
/RMII_MDC: U1.16 (PC1); also elsewhere on the board
/RMII_MDIO: U1.25 (PA2); also elsewhere on the board
/RMII_REF_CLK: U1.24 (PA1); also elsewhere on the board
/RMII_RXD0: U1.33 (PC4); also elsewhere on the board
/RMII_RXD1: U1.34 (PC5); also elsewhere on the board
/RMII_TXD0: U1.51 (PB12); also elsewhere on the board
/RMII_TXD1: U1.52 (PB13); also elsewhere on the board
/RMII_TXEN: U1.48 (PB11); also elsewhere on the board
/VDDA: C18.1, C19.1, J5.8, L1.2, U1.21 (VREF+), U1.22 (VDDA)
/VDD_POE: J8.9 (V+); also elsewhere on the board
/VSS_POE: J8.10 (V-); also elsewhere on the board
GND: C1.1, C2.1, C3.2, C4.2, C5.1, C6.1, C7.2, C8.2, C9.2, C10.2, C11.2, C12.2, C13.2, C14.2, C15.2, C16.2, C18.2, C19.2, C20.2, C21.2, C32.2, J2.3, J3.6, J3.7, J5.7, J7.4, J7.6, J7.8, J7.10, J7.12, J7.14, J7.16, J7.18, J7.20, R10.2, R14.2, SW1.2, U1.10 (VSS), U1.20 (VSSA), U1.27 (VSS), U1.74 (VSS), U1.99 (VSS); also elsewhere on the board
unnamed: J8.13 (G+), R2.2
unnamed: R8.2, U1.94 (BOOT0)
unnamed: R10.1, U1.37 (PB2)
unnamed: C21.1, U1.8 (PC14), Y2.2
unnamed: C32.1, U1.9 (PC15), Y2.1
unnamed: C5.2, R9.1, U1.12 (PH0), Y1.2
unnamed: C6.2, R9.2, U1.13 (PH1), Y1.1
unnamed: C8.1, U1.49 (VCAP_1)
unnamed: C9.1, U1.73 (VCAP_2)

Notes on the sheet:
Mounting Hardware
Power
JTAG
Processor
Daughterboard
Ethernet

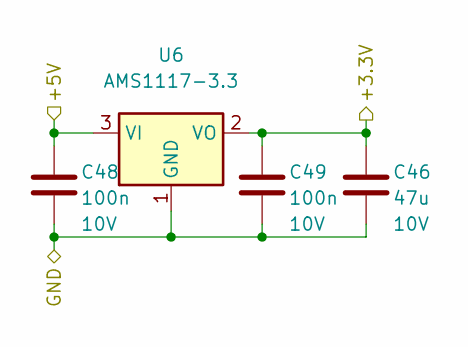
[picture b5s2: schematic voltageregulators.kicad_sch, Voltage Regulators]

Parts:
C46: 47u; C_1206_3216Metric; Voltage Rating 10V; LCSC PN C96123
C48, C49: 100n; C_0603_1608Metric; Voltage Rating 10V; LCSC PN C14663
U6: AMS1117-3.3; SOT-223-3_TabPin2; LCSC PN C6186

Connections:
+3.3V: C46.1, C49.1, U6.2 (VO); also elsewhere on the board
+5V: C48.1, U6.3 (VI); also elsewhere on the board
GND: C46.2, C48.2, C49.2, U6.1 (GND); also elsewhere on the board

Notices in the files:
boards/motherboard/motherboard.kicad_pcb:
Licensed CERN-OHL-S v2
